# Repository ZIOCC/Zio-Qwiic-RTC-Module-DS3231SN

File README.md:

# Zio Qwiic RTC Module (DS3231SN)

> This product can be available for purchase [here](https://www.smart-prototyping.com/Zio-Qwiic-RTC-module-DS3231).

#### Description

This ZIO module features a low power real-time clock battery backed based on the DS3231SN IC. This board has a high precision and fast I2C (400kHZ) bus with an integrated temperature compensated 32KHz crystal oscillator (TCXO) and crystal. The TCXO provides a stable and accurate reference clock, and maintains the RTC to within ±2 minutes per year accuracy
from -40°C to +85°C.

The real-time clock counts seconds, minutes, hours a day, date, month and year with leap year compensation. The clock operates either the 4-hour to 12-hour format (which includes AM/PM indicator). It also compensate the month days, and the date is automatically adjusted at the end of the month. Some other cool features in this little board, it provides two programmable time-of-day alarms and a programmable square-wave output (check the [datasheet](https://datasheets.maximintegrated.com/en/ds/DS3231.pdf) to set the corresponding registers)

Make readings is pretty simple since all the communication is via I2C integrating the Qwiic connect system, but as most of our boards, we included the pinout in case you want to use a breadboard. The TCXO frequency output is available at the 32kHz pinout.

#### Specification

* Supply Voltage: 3.3V
* Current Consumption: 200μA
* Interface: I2C
* Battery Backup
* 32KHz crystal oscillator
* Operating Temperature Range -40°C to +85°C
* Low-Power Consumption
* Real-Time Clock Counts Seconds, Minutes, Hours, Day, Date, Month, and Year with Leap Year Compensation Valid Up to 2100
* Two Time-of-Day Alarms
* Programmable Square-Wave Output
* IC:DS3231SN
* I2C address: 0x68
* Dimensions: 30.1 x 36.4mm
* Weight:4.7g

#### Links

* [Eagle File and Schematic](https://github.com/ZIOCC/Zio-Qwiic-RTC-Module-DS3231SN)
* [Library Link](https://github.com/adafruit/RTClib)
* [DS3231 Datasheet](https://datasheets.maximintegrated.com/en/ds/DS3231.pdf)

> ###### About Zio
> Zio is a new line of open sourced, compact, and grid layout boards, fully integrated for Arduino and Qwiic ecosystem. Designed ideally for wearables, robotics, small-space limitations or other on the go projects. Check out other awesome Zio products [here](https://www.smart-prototyping.com/Zio).

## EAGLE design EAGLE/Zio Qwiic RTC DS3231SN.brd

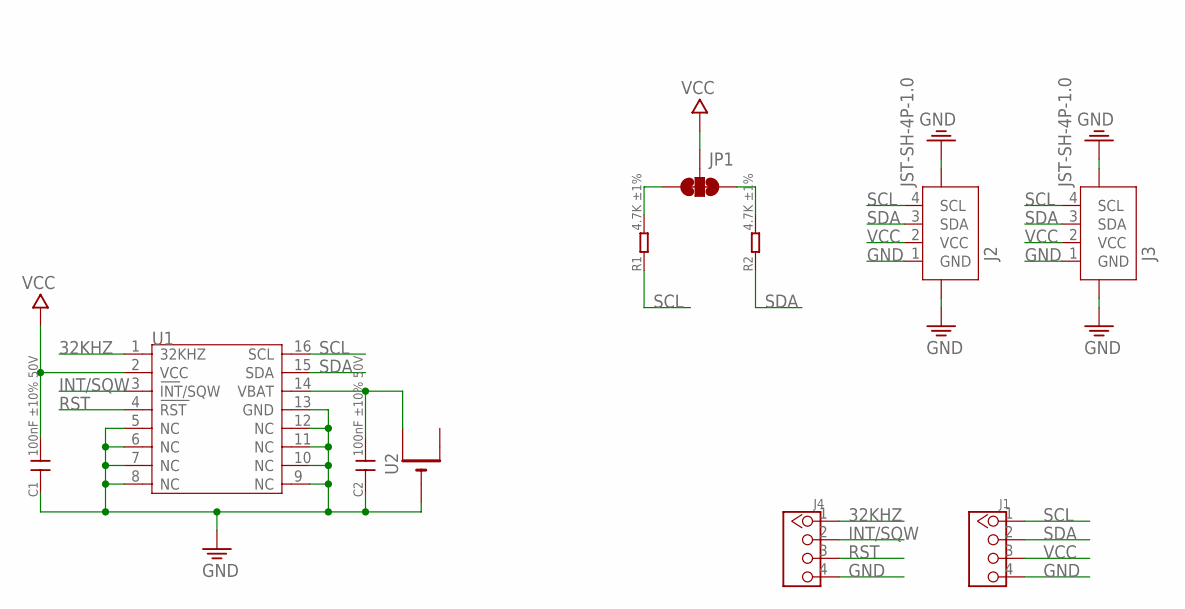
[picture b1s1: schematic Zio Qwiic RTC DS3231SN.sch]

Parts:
C1, C2: 100nF ±10% 50V; C0603
J1, J4: HEADER-4P-60/35MIL; 4P-65/35MIL
J2, J3: JST-SH-4P-1.0; JST-SH-4P
JP1: SMT-JUMPER_3_2-NC_TRACE
R1, R2: 4.7K ±1%; R0603
U1: DS3231; SO16-W
U2: CR1220SMT; CR1220-SMD

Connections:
32KHZ: J4.1, U1.1 (32KHZ)
GND: C1.1, C2.1, J1.4, J2.1 (GND), J2.NC1 (5), J2.NC2 (6), J3.1 (GND), J3.NC1 (5), J3.NC2 (6), J4.4, U1.5 (NC), U1.6 (NC), U1.7 (NC), U1.8 (NC), U1.9 (NC), U1.10 (NC), U1.11 (NC), U1.12 (NC), U1.13 (GND), U2.-
INT/SQW: J4.2, U1.3 (INT/SQW)
unnamed: C2.2, U1.14 (VBAT), U2.+$1 (+)
unnamed: JP1.3, R1.2
unnamed: JP1.1, R2.2
RST: J4.3, U1.4 (RST)
SCL: J1.1, J2.4 (SCL), J3.4 (SCL), R1.1, U1.16 (SCL)
SDA: J1.2, J2.3 (SDA), J3.3 (SDA), R2.1, U1.15 (SDA)
VCC: C1.2, J1.3, J2.2 (VCC), J3.2 (VCC), JP1.2, U1.2 (VCC)

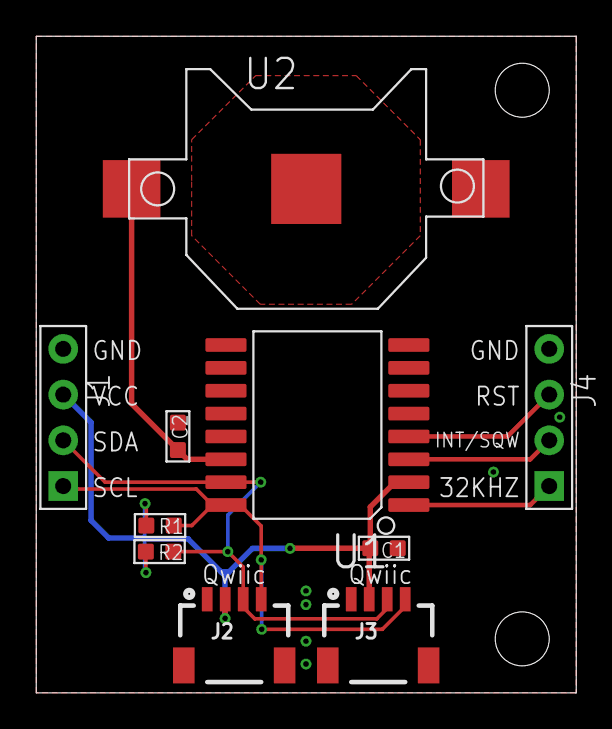
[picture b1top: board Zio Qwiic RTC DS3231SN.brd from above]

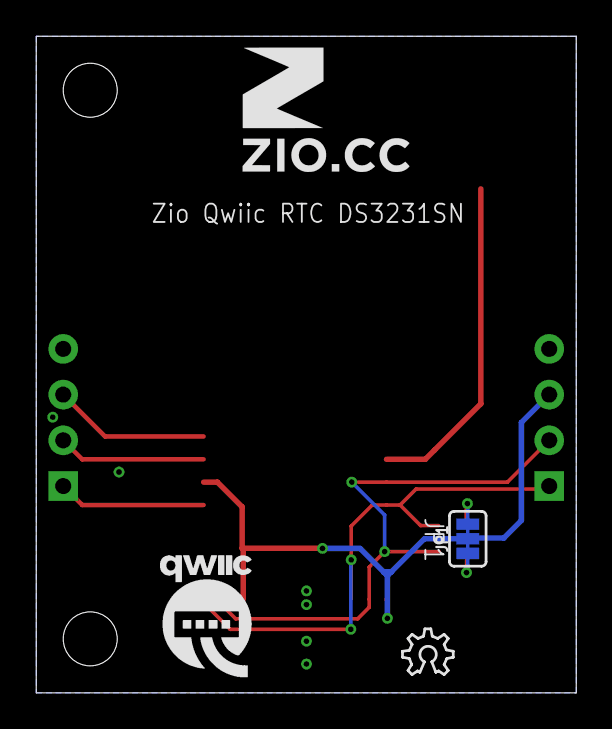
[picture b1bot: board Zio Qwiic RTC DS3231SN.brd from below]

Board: 2 copper layers, 30.0 x 36.5 mm, 14 parts (4 on the bottom side), 10 nets.

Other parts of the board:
U$1: 7MM
U$4: OSHW_6X100_NOTEXT
U$6: QWIIC-LOGO-MEDIUM
